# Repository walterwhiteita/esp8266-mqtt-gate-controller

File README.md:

# MQTT-ESPGate: Retrofit Solution for Gate Control Boards

Welcome to the ESPGate repository! This project offers a comprehensive retrofit solution tailored to upgrade a variety of gate control boards. Leveraging the power of MQTT and ESP8266 modules, this solution provides seamless control over gate automation systems. The repository hosts the design files and documentation for a specialized PCB crafted specifically for this purpose, ensuring easy integration and enhanced functionality for existing gate control setups.

## Project Description

The project aims to upgrade existing automatic gates by adding advanced control and monitoring features. The provided PCB is designed to be integrated into the control boards of installed gates, providing a standardized interface for adding new functionalities without the need to replace the entire system.

## Key Features

- **Remote Commands**: The PCB allows sending remote commands to the gate, enabling opening, closing, and other programmable actions.
- **Status Monitoring**: It's possible to read the current status of the gate, including open, closed signals, and error states.
- **Addition of Clean Contact**: The option to add a clean contact is provided, allowing integration with external control systems or safety devices.

## Repository Structure

- `design/`: Contains PCB design files, including schematics and layouts.
- `docs/`: Additional project documentation.
- `examples/`: Code examples for interfacing with the PCB.
- `LICENSE`: Project license.
- `README.md`: This documentation file.

## Hardware and Software Requirements

### Hardware

- **Opening and Closing Contacts**: The opening and closing contacts present on the gate control board are essential for sending opening and closing commands through our PCB.
- **Indicator Light (optional)**: If available, the indicator light provides visual feedback on the gate's status. In cases where the indicator light is not available, the clean contact already present on our PCB can be used to connect a sensor that detects the gate's open or closed status.

### Software

- **WiFi Connection**: A WiFi connection is required to facilitate communication between the PCB and the MQTT broker, as well as for any configuration operations via mobile devices or computers.
- **MQTT Broker**: An MQTT broker must be available and running, acting as an intermediary for communication between the PCB and other devices or services.

These hardware and software requirements are essential to ensure the proper and reliable operation of the gate control system through the PCB.

## Contributions

Contributions to this project are welcome. Please follow the contribution guidelines described in the `CONTRIBUTING.md` file.

## License

This project is licensed under the [GNU General Public License v3.0](LICENSE). Please refer to the license file for further information.

## Contact

For questions, bug reports, or other inquiries, please contact [Repository Owner's Name](mailto:dimieri00@gmail.com).

---
© 2024 [Repository Owner's Name](https://github.com/walterwhiteita)

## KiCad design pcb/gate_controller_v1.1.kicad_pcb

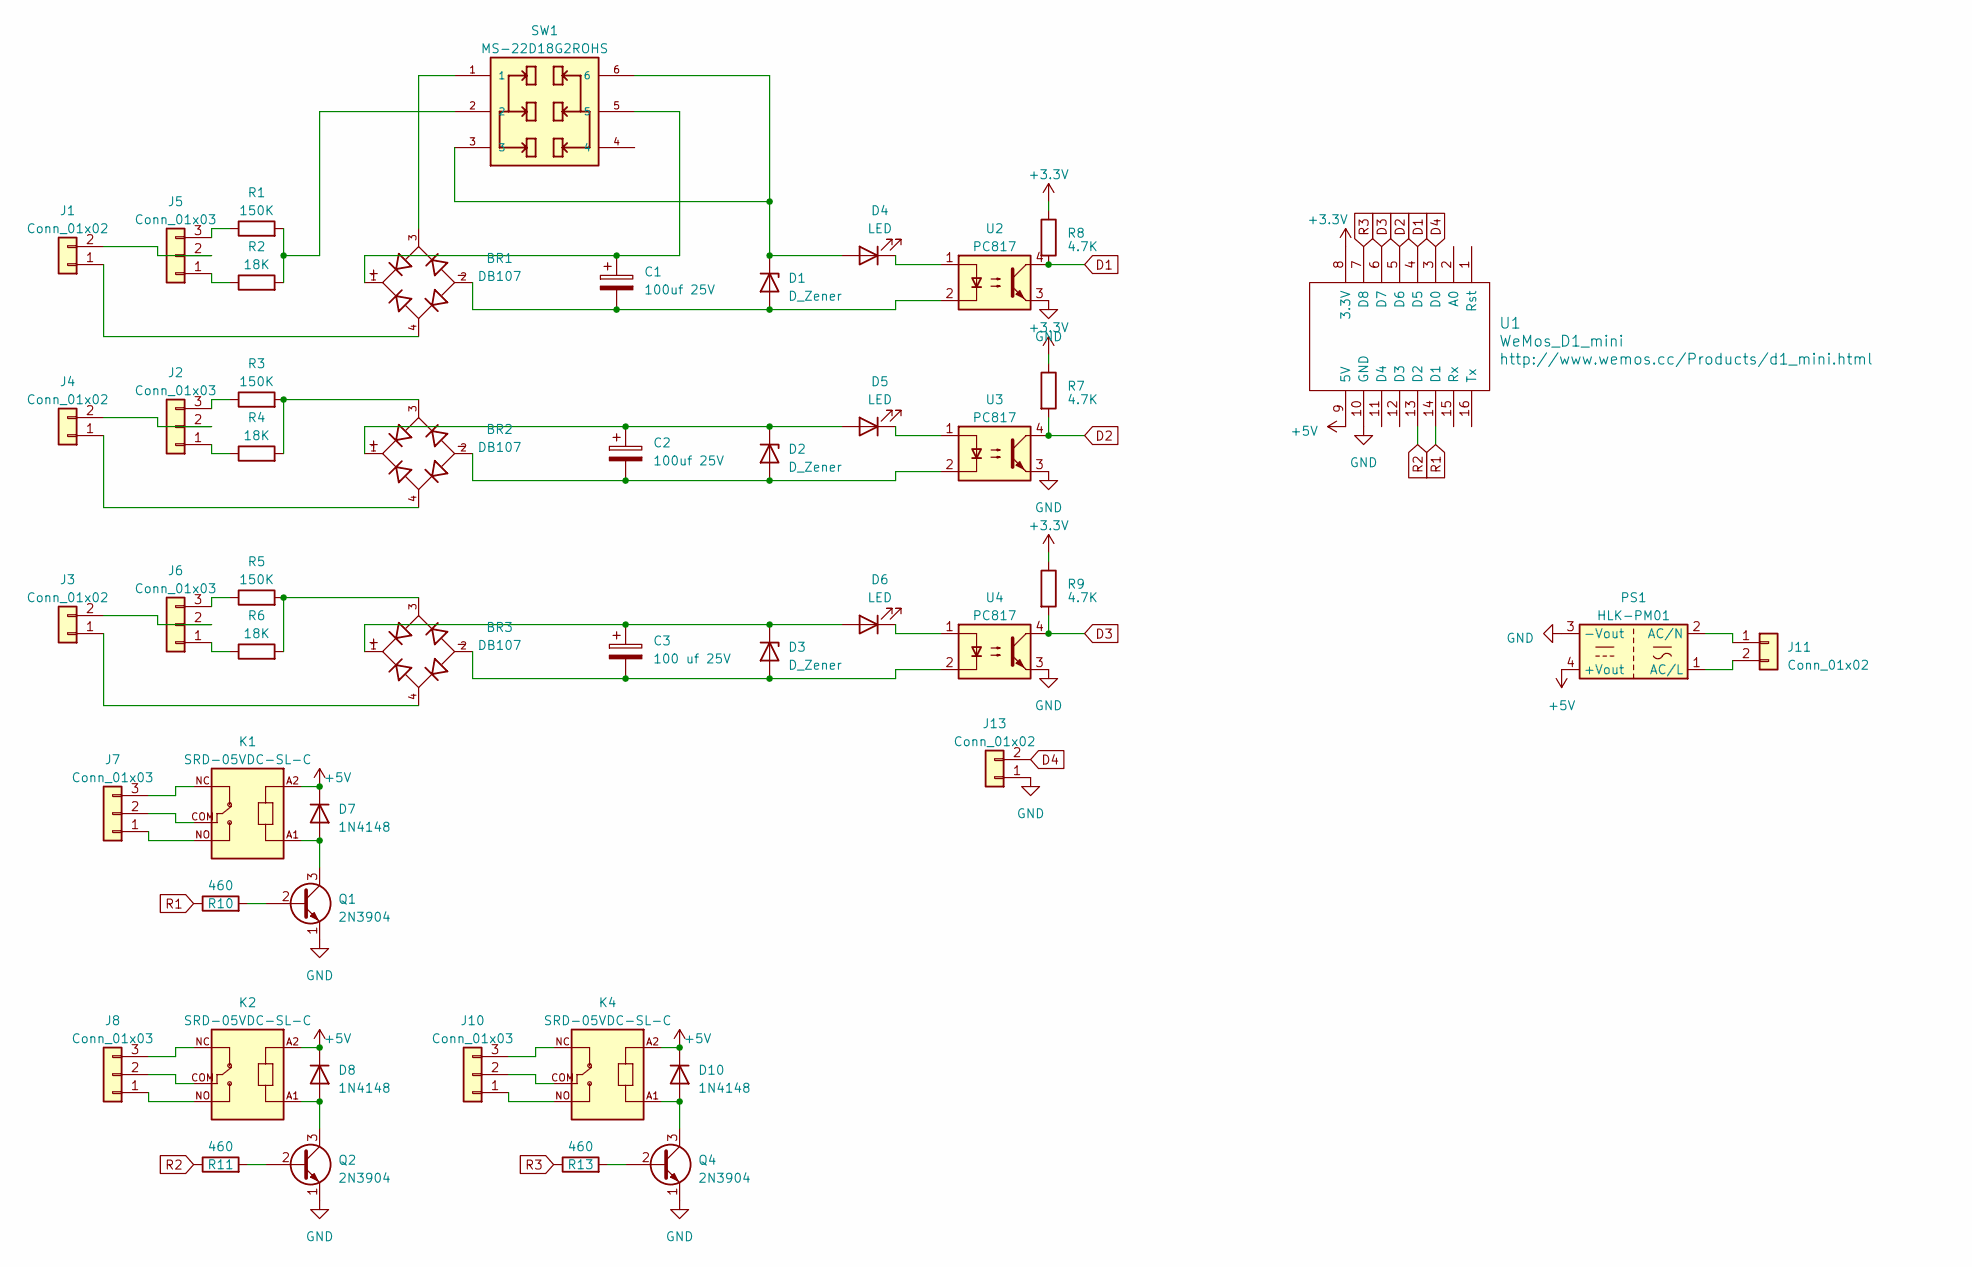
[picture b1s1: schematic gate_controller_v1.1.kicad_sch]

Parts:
BR1, BR2, BR3: DB107; DIP825W50P509L880H320Q4; PARTREV 13
C1, C2: 100uf 25V; CP_Radial_D6.3mm_P2.50mm
C3: 100 uf 25V; CP_Radial_D6.3mm_P2.50mm
D1, D2, D3: D_Zener; D_DO-41_SOD81_P2.54mm_Vertical_AnodeUp
D4, D5, D6: LED; LED_D5.0mm
D7, D8, D10: 1N4148; D_DO-35_SOD27_P7.62mm_Horizontal
J1, J3, J4, J11: Conn_01x02; TerminalBlock_bornier-2_P5.08mm
J2, J5, J6: Conn_01x03; PinHeader_1x03_P2.54mm_Vertical
J7, J8, J10: Conn_01x03; TerminalBlock_bornier-3_P5.08mm
J13: Conn_01x02; PhoenixContact_MCV_1,5_2-G-3.81_1x02_P3.81mm_Vertical
K1, K2, K4: SRD-05VDC-SL-C; RELAY_SRD-05VDC-SL-C
PS1: HLK-PM01; Converter_ACDC_HiLink_HLK-PMxx
Q1, Q2, Q4: 2N3904; TO-92_Inline
R1, R3, R5: 150K; R_Axial_DIN0414_L11.9mm_D4.5mm_P20.32mm_Horizontal
R2, R4, R6: 18K; R_Axial_DIN0414_L11.9mm_D4.5mm_P20.32mm_Horizontal
R7, R8, R9: 4.7K; R_Axial_DIN0207_L6.3mm_D2.5mm_P2.54mm_Vertical
R10, R11, R13: 460; R_Axial_DIN0207_L6.3mm_D2.5mm_P2.54mm_Vertical
SW1: MS-22D18G2ROHS; SW_MS-22D18G2ROHS
U1: WeMos_D1_mini; wemos-d1-mini-connectors-only
U2, U3, U4: PC817; DIP-4_W7.62mm

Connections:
+3.3V: R7.1, R8.1, R9.1, U1.8 (3.3V)
+5V: D7.1 (K), D8.1 (K), D10.1 (K), K1.A2, K2.A2, K4.A2, PS1.4 (+Vout), U1.9 (5V)
D1: R8.2, U1.4 (D5), U2.4
D2: R7.2, U1.5 (D6), U3.4
D3: R9.2, U1.6 (D7), U4.4
D4: J13.2, U1.3 (D0)
GND: J13.1, PS1.3 (-Vout), Q1.1 (E), Q2.1 (E), Q4.1 (E), U1.10 (GND), U2.3, U3.3, U4.3
unnamed: BR1.1, C1.1, SW1.5
unnamed: BR1.3, SW1.1
unnamed: BR2.3, R3.2, R4.2
unnamed: BR3.3, R5.2, R6.2
unnamed: BR1.2, C1.2, D1.2 (A), U2.2
unnamed: D1.1 (K), D4.2 (A), SW1.3, SW1.6
unnamed: BR2.2, C2.2, D2.2 (A), U3.2
unnamed: BR2.1, C2.1, D2.1 (K), D5.2 (A)
unnamed: BR3.2, C3.2, D3.2 (A), U4.2
unnamed: BR3.1, C3.1, D3.1 (K), D6.2 (A)
unnamed: D4.1 (K), U2.1
unnamed: D5.1 (K), U3.1
unnamed: D6.1 (K), U4.1
unnamed: D7.2 (A), K1.A1, Q1.3 (C)
unnamed: D8.2 (A), K2.A1, Q2.3 (C)
unnamed: D10.2 (A), K4.A1, Q4.3 (C)
unnamed: BR1.4, J1.1
unnamed: J1.2, J5.2
unnamed: J2.1, R4.1
unnamed: J2.2, J4.2
unnamed: J2.3, R3.1
unnamed: BR3.4, J3.1
unnamed: J3.2, J6.2
unnamed: BR2.4, J4.1
unnamed: J5.1, R2.1
unnamed: J5.3, R1.1
unnamed: J6.1, R6.1
unnamed: J6.3, R5.1
unnamed: J7.1, K1.NO
unnamed: J7.2, K1.COM
unnamed: J7.3, K1.NC
unnamed: J8.1, K2.NO
unnamed: J8.2, K2.COM
unnamed: J8.3, K2.NC
unnamed: J10.1, K4.NO
unnamed: J10.2, K4.COM
unnamed: J10.3, K4.NC
unnamed: J11.1, PS1.2 (AC/N)
unnamed: J11.2, PS1.1 (AC/L)
unnamed: Q1.2 (B), R10.2
unnamed: Q2.2 (B), R11.2
unnamed: Q4.2 (B), R13.2
unnamed: R1.2, R2.2, SW1.2
R1: R10.1, U1.14 (D1)
R2: R11.1, U1.13 (D2)
R3: R13.1, U1.7 (D8)

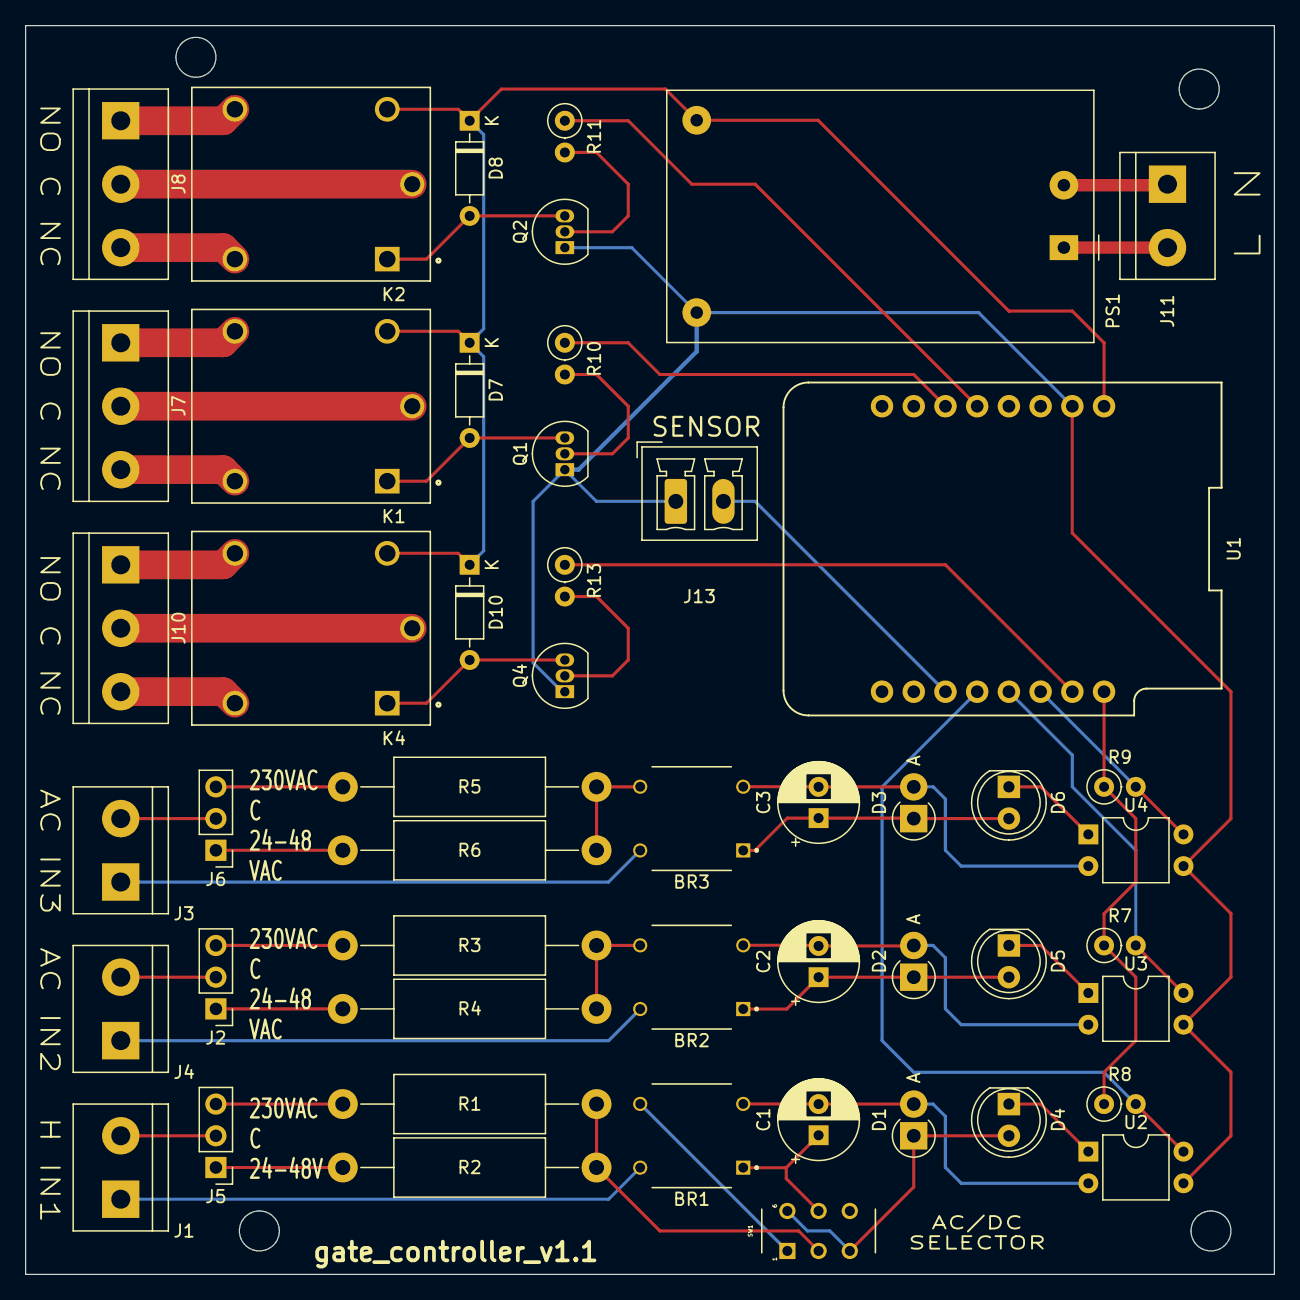
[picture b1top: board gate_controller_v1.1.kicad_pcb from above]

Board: 2 copper layers, 100.0 x 100.0 mm, 50 parts (0 on the bottom side), 53 nets.

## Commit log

2024-02-26 Add files via upload
    KiCad PCB
2024-02-26 Add files via upload
    PDF
2024-02-28 First upload
2024-03-11 Upload firmware
2024-03-12 organizzazione file migliorata esponenzialmente!!!!
2024-03-13 separazione file e funzioni
2024-03-14 update firmware
2024-03-18 Some update
2024-03-19 Changed pin
2024-03-19 update to gitignore
2024-03-21 update to mqtt
2024-03-21 some update to server functions
2024-03-21 pcb_v1.1
    fixed gpio
    added:
    - ac/dc mode selector
    - sensor contact
